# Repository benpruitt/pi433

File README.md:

# pi433

Raspberry Pi Zero-based Etekcity 433 MHz wireless outlet control. Repo contains
control code and PCB designs.

## Features

* On/off control of Etekcity 433 MHz outlets
* Configurable via a single JSON file
* Ability to group switches into functional groups (e.g., "living room lights")
* Integration with Amazon Echo voice control
* RESTful API exposes outlet control
* Lightweight mobile frontend for manual control

## Dependencies

* [C] wiringPi
* [Python] Cython [optional]
* [Python] gevent
* [Python] rpi.GPIO

## Installation

The latest Rasbian image should include several of the dependencies, including
`RPi-GPIO` and `wiringPi`. The wifi on the Pi zero daughterboard is provided
by an ESP-12F that the Broadcom chip talks to over an SDIO interface. Here
are instructions for updating the device tree & building the module to
support the ESP-12F: https://oshlab.com/esp8266-raspberry-pi-gpio-wifi/

After following the above instructions just set up wifi as usual by editing
`/etc/network/interfaces` and `/etc/wpa_supplicant/wpa_supplicant.conf`.

Next install the remaining python dependencies. I would recommend using
`apt-get` rather than `pip` (to avoid compile times) if you don't mind
installing in your system site packages directory.

Finally:

`sudo python install.py`
_(admin privileges necessary to install systemd service)_

## Installation notes

`pi433` is tested on Raspian under the system Python (2.7.7) / in a
virtual env. `pi433` is not installed into the Python site packages
directory, but rather is copied into `~/.pi433`. The install script copies
the main module directory along with the cli into `~/.pi433` and creates /
configures the `systemd` service necessary to run `pi433` at startup.

The repo contains a pre-built version of the Cython wrapper for the rc-switch
library, so unless you make modifications you shouldn't need Cython. (although
if you do need it, make sure you install via `sudo apt-get install cython`
to avoid the lonnnngg build time you'll experience through `pip`).

## Configuration

The included `config.json` file is also copies into `~/.pi433` and contains
the specifications for the RF outlets / groups that you want to control.

## Todo

* Include RF sniffing interface
* Implement config button functionality
* Better antenna for TX

## Licensing

All code is released under the MIT license with the exception of:

* Unmodified source code from rc-switch is LGPL v2.1:

        pi433/RCSwitch.cpp
        pi433/RCSwitch.h

## Acknowledgements

Inspired by (and derived from [see code comments]):
* rc-switch - https://github.com/sui77/rc-switch
* fauxmo - https://github.com/makermusings/fauxmo / https://github.com/n8henrie/fauxmo

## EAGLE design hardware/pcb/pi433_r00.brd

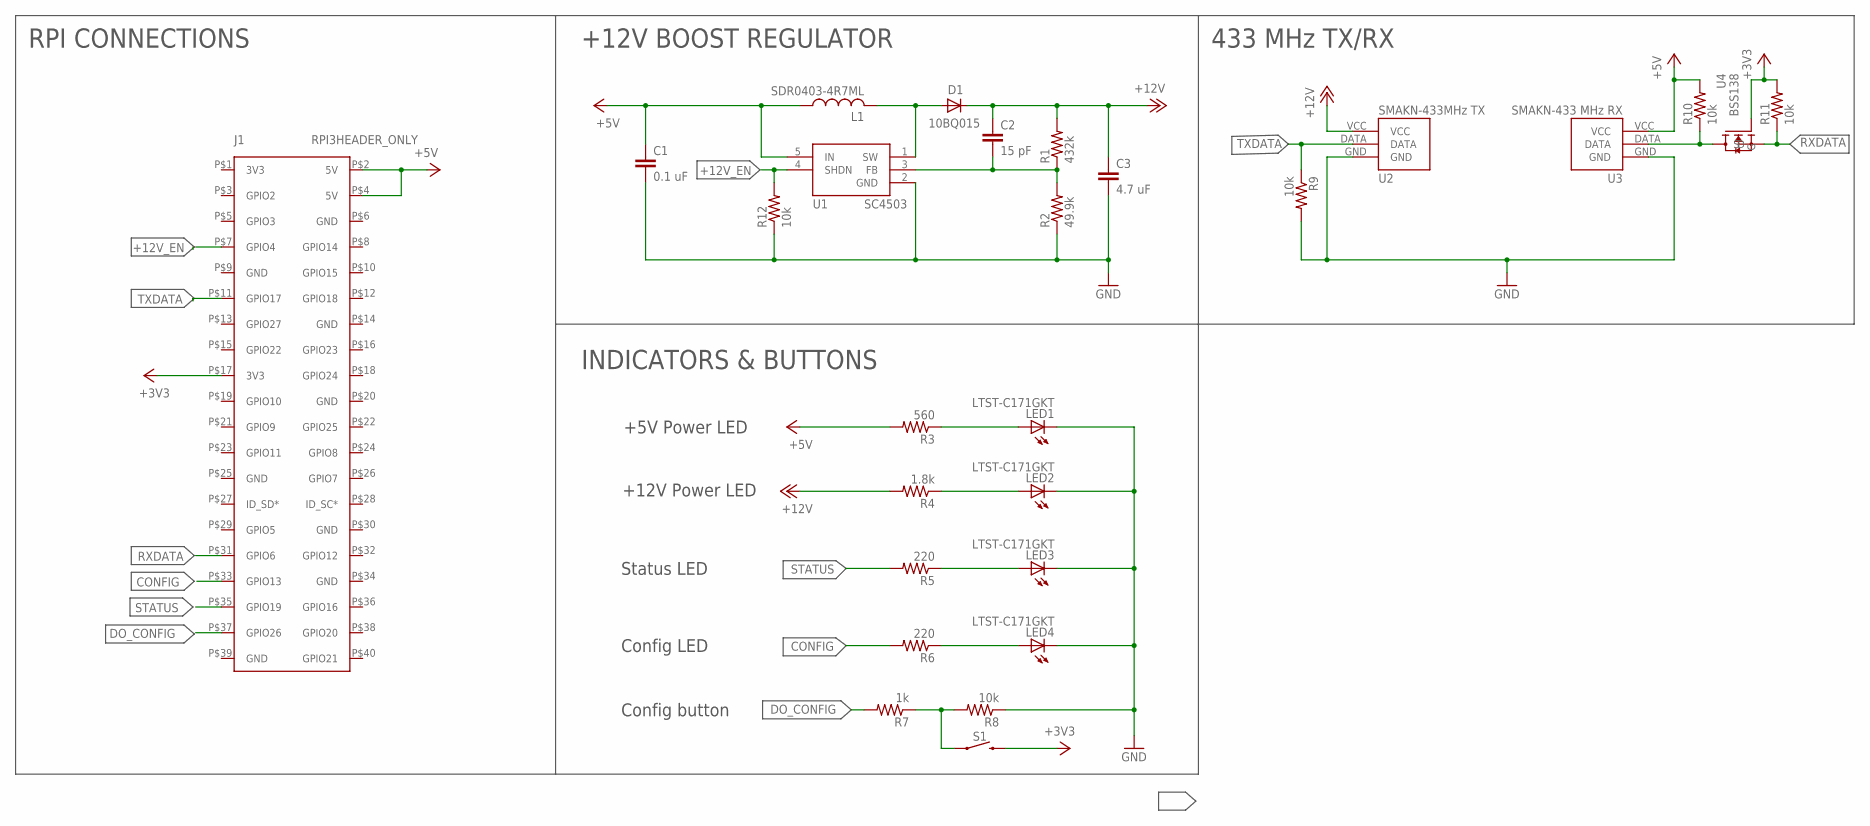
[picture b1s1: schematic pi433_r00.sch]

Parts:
C1: 0.1 uF; C0603
C2: 15 pF; C0603
C3: 4.7 uF; C0805
D1: 10BQ015; DO214AA
J1: RPI3HEADER_ONLY; RPI3-HEADER_ONLY
L1: SDR0403-4R7ML; SDR0403
LED1, LED2, LED3, LED4: LTST-C171GKT; CHIPLED_0805
R1: 432k; R0805
R2: 49.9k; R0805
R3: 560; R0805
R4: 1.8k; R0805
R5, R6: 220; R0805
R7: 1k; R0805
R8, R9, R10, R11, R12: 10k; R0805
S1: MOMENTARY-SWITCH-SPST-SMD-6.0X3.5MM; TACTILE_SWITCH_SMD_6.0X3.5MM
U1: SC4503; TSOT-23-5
U2: SMAKN-433TX
U3: SMAKN-433RX
U4: BSS138

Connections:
+3V3: J1.P$17 (3V3), R11.2, S1.2, U4.G
+5V: C1.1, J1.P$2 (5V), J1.P$4 (5V), L1.P$1 (1), R3.2, R10.2, U1.5 (IN), U3.VCC
+12V: C2.1, C3.1, D1.C, R1.2, R4.2, U2.VCC
+12V_EN: J1.P$7 (GPIO4), R12.2, U1.4 (SHDN)
CONFIG: J1.P$33 (GPIO13), R6.2
DO_CONFIG: J1.P$37 (GPIO26), R7.2
GND: C1.2, C3.2, LED1.C, LED2.C, LED3.C, LED4.C, R2.1, R8.1, R9.2, R12.1, U1.2 (GND), U2.GND, U3.GND
unnamed: LED1.A, R3.1
unnamed: D1.A, L1.P$2 (2), U1.1 (SW)
unnamed: LED2.A, R4.1
unnamed: LED3.A, R5.1
unnamed: C2.2, R1.1, R2.2, U1.3 (FB)
unnamed: LED4.A, R6.1
unnamed: R7.1, R8.2, S1.1
unnamed: R10.1, U3.DATA, U4.D
RXDATA: J1.P$31 (GPIO6), R11.1, U4.S
STATUS: J1.P$35 (GPIO19), R5.2
TXDATA: J1.P$11 (GPIO17), R9.1, U2.DATA

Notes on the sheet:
RPI CONNECTIONS
+12V BOOST REGULATOR
+5V Power LED
+12V Power LED
Status LED
INDICATORS & BUTTONS
Config LED
Config button
433 MHz TX/RX

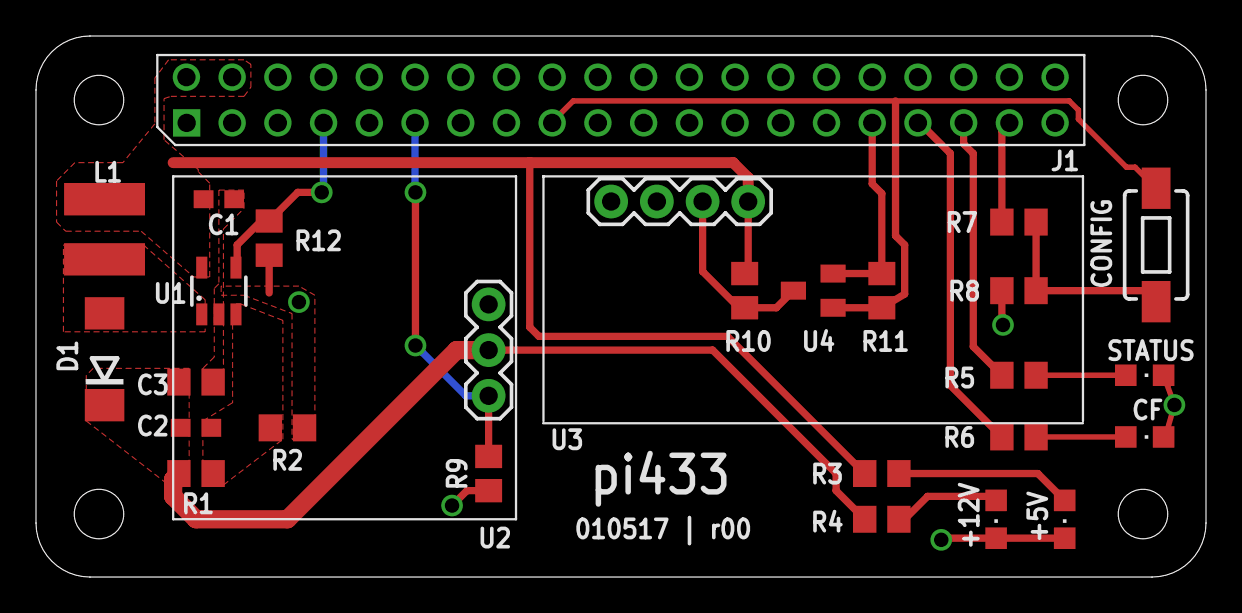
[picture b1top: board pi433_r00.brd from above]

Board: 2 copper layers, 65.0 x 30.1 mm, 27 parts (0 on the bottom side), 18 nets.

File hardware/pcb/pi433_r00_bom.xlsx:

UID | REF | PART TYPE | #/BOARD | DES | MFG DES | MFG P/N | MFG | SUPPLIER | SUPPLIER P/N | UNIT SIZE | $/UNIT | $/BOARD | DIGIKEY ORDER 1/7/16
PI433_00_01 | R1 | Resistor | 1 | 0805 432k | RES SMD 432K OHM 1% 1/8W 0805 | RC0805FR-07432KL | Yageo | Digikey | 311-432KCRCT-ND | 1 | 0.1 | 0.1 | 4
PI433_00_02 | R2 | Resistor | 1 | 0805 49.9k | RES SMD 49.9K OHM 1% 1/8W 0805 | RC0805FR-0749K9L | Yageo | Digikey | 311-49.9KCRCT-ND | 1 | 0.1 | 0.1 | 4
PI433_00_03 | R3 | Resistor | 1 | 0805 560 | RES SMD 560 OHM 1% 1/8W 0805 | RC0805FR-07560RL | Yageo | Digikey | 311-560CRCT-ND | 1 | 0.1 | 0.1 | 4
PI433_00_04 | R4 | Resistor | 1 | 0805 1.8k | RES SMD 1.8K OHM 1% 1/8W 0805 | RC0805FR-071K8L | Yageo | Digikey | 311-1.80KCRCT-ND | 1 | 0.1 | 0.1 | 4
PI433_00_05 | R5, R6 | Resistor | 2 | 0805 220 | RES SMD 220 OHM 1% 1/8W 0805 | RC0805FR-07220RL | Yageo | Digikey | 311-220CRCT-ND | 1 | 0.1 | 0.2 | 8
PI433_00_06 | R7 | Resistor | 1 | 0805 1k | RES SMD 1K OHM 1% 1/8W 0805 | RC0805FR-071KL | Yageo | Digikey | 311-1.00KCRCT-ND | 1 | 0.1 | 0.1 | 4
PI433_00_07 | R8, R9, R10, R11, R12 | Resistor | 5 | 0805 10k | RES SMD 10K OHM 1% 1/8W 0805 | RC0805FR-0710KL | Yageo | Digikey | 311-10.0KCRCT-ND | 1 | 0.1 | 0.5 | 20
PI433_00_08 | C1 | Capacitor | 1 | 0603 0.1 uF | CAP CER 1UF 10V X5R 0603 | GRM188R61A105K | Murata | Digikey | 490-6408-1-ND | 1 | 0.1 | 0.1 | 4
PI433_00_09 | C2 | Capacitor | 1 | 0603 15 pF | CAP CER 15PF 50V NP0 0603 | GCM1885C1H150JA16D | Murata | Digikey | 490-4957-1-ND | 1 | 0.1 | 0.1 | 4
PI433_00_10 | C3 | Capacitor | 1 | 0603 4.7 uF | CAP CER 4.7UF 16V X5R 0805 | GRM21BR61C475K | Murata | Digikey | 490-7214-1-ND | 1 | 0.17 | 0.17 | 4
PI433_00_11 | L1 | Inductor | 1 | 4.7 uH 1.7 A | FIXED IND 4.7UH 1.7A 94 MOHM SMD | SDR0403-4R7ML | Bourns | Digikey | SDR0403-4R7MLCT-ND | 1 | 0.47 | 0.47 | 4
PI433_00_12 | U1 | Regulator | 1 | 1.4A boost | IC REG BOOST ADJ 1.4A TSOT23-5 | SC4503TSKTRT | Semtech | Digikey | SC4503TSKCT-ND | 1 | 1.92 | 1.92 | 4
PI433_00_13 | U2, U3 | 433 MHz Transmitter / Receiver | 1 | 433 MHz Transmitter / Receiver | N/A | N/A | SMAKN | Amazon | B00M2CUALS | 1 | 6.66 | 6.66
PI433_00_14 | U4 | MOSFET | 1 | Level coversion MOSFET | MOSFET N-CH 50V 220MA SOT-23 | BSS138 | Fairchild | Digikey | BSS138CT-ND | 1 | 0.22 | 0.22 | 4
PI433_00_15 | S1 | Switch | 1 | Tactile switch | SWITCH TACTILE SPST-NO 0.05A 12V | RS-032G05A3-SM RT | C&K | Digikey | CKN10388CT-ND | 1 | 0.56000000000000005 | 0.56000000000000005 | 4
PI433_00_16 | LED1, LED2, LED3, LED4 | LED | 4 | LED | LED GREEN CLEAR 0805 SMD | LTST-C171GKT | Lite-On | Digikey | 160-1423-1-ND | 1 | 0.28999999999999998 | 1.1599999999999999 | 16

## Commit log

2017-02-12 rename arg for byteify
2017-02-13 add pdf version of r01 pcb design, update readme
2017-02-13 add inline attributions
2017-02-13 add esp12-f to r01 bom
2017-02-13 timing optimizations
2019-08-18 remove ssdp server
2019-08-18 properly pass pulse_length into sendRFCode
2019-08-18 fixup
2019-08-18 replace flask with quart
2019-08-18 temporary changes to pi433.py

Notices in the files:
parts and their libraries:
SparkFun-Switches: Licensing: Creative Commons ShareAlike 4.0 International - https://creativecommons.org/licenses/by-sa/4.0
